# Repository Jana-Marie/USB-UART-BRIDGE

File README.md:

# USB-UART-BRIDGE

Smol and friendly USB-UART-BRIDGE & ESP32 programmer with Tag-Connect 2030 Connector :3

[KiCAD lib](https://github.com/Jana-Marie/ESP-TC-PROG/tree/main/KiCAD-libs)

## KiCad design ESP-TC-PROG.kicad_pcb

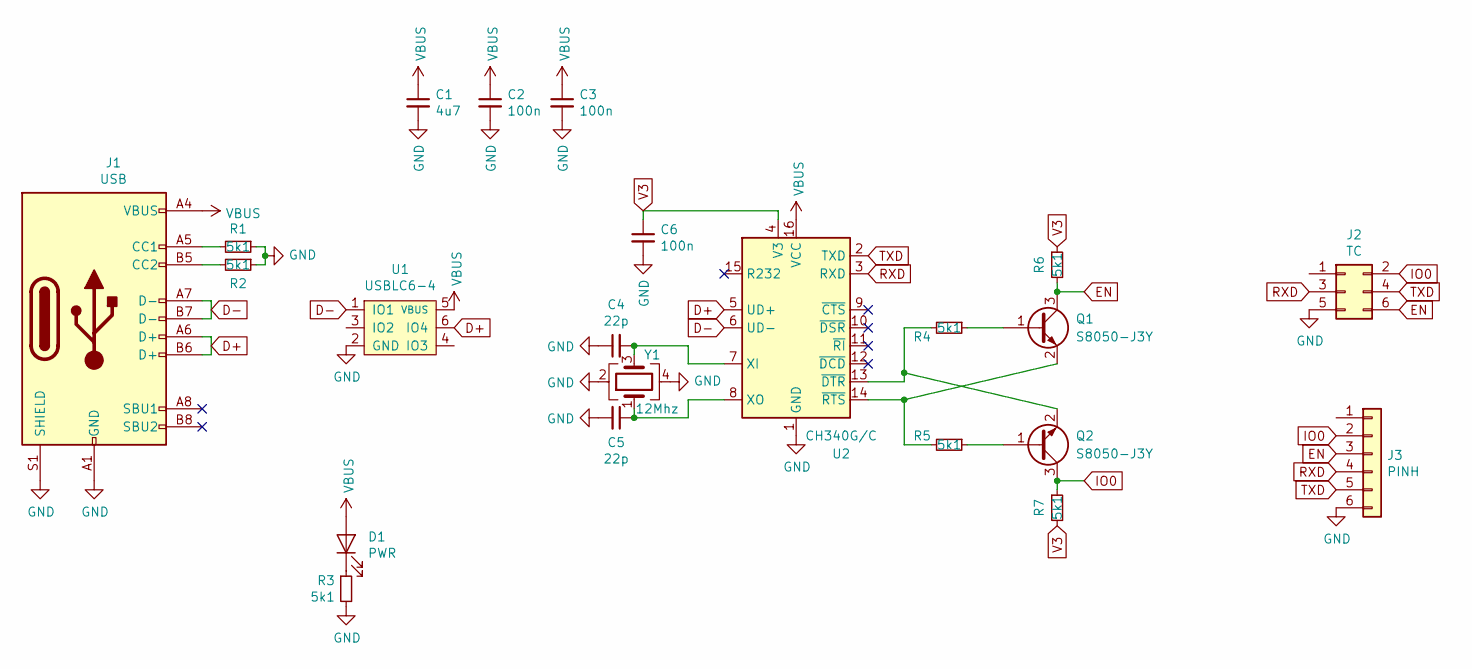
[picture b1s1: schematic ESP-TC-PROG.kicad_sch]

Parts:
C1: 4u7; C_0805
C2, C3, C6: 100n; C_0402
C4, C5: 22p; C_0402
D1: PWR; LED_0603_1608Metric
J1: USB; USB-C 16Pin
J2: TC; IDC-Header_2x03_P2.54mm_Vertical_center
J3: PINH; PinHeader_1x06_P2.54mm_Vertical_center
Q1, Q2: S8050-J3Y; SOT-23
R1, R2, R3, R4, R5, R6, R7: 5k1; R_0402
U1: USBLC6-4; SOT-23-6
U2: CH340G/C; SOIC-16_3.9x9.9mm_P1.27mm
Y1: 12Mhz; Crystal_SMD_3225-4Pin_3.2x2.5mm

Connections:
D+: J1.A6 (D+), J1.B6 (D+), U1.6 (IO4), U2.5 (UD+)
D-: J1.A7 (D-), J1.B7 (D-), U1.1 (IO1), U2.6 (UD-)
EN: J2.6, J3.3, Q1.3 (C), R6.2
GND: C1.2, C2.2, C3.2, C4.1, C5.2, C6.2, J1.A1 (GND), J1.A12 (GND), J1.B1 (GND), J1.B12 (GND), J1.S1 (SHIELD), J2.5, J3.6, R1.1, R2.1, R3.2, U1.2 (GND), U2.1 (GND), Y1.2, Y1.4
IO0: J2.2, J3.2, Q2.3 (C), R7.1
unnamed: C4.2, U2.7 (XI), Y1.3
unnamed: C5.1, U2.8 (XO), Y1.1
unnamed: D1.1 (K), R3.1
unnamed: J1.A5 (CC1), R1.2
unnamed: J1.B5 (CC2), R2.2
unnamed: Q1.1 (B), R4.1
unnamed: Q1.2 (E), R5.2, U2.14 (~RTS)
unnamed: Q2.1 (B), R5.1
unnamed: Q2.2 (E), R4.2, U2.13 (~DTR)
RXD: J2.3, J3.4, U2.3 (RXD)
TXD: J2.4, J3.5, U2.2 (TXD)
V3: C6.1, R6.1, R7.2, U2.4 (V3)
VBUS: C1.1, C2.1, C3.1, D1.2 (A), J1.A4 (VBUS), J1.A9 (VBUS), J1.B4 (VBUS), J1.B9 (VBUS), U1.5 (VBUS), U2.16 (VCC)

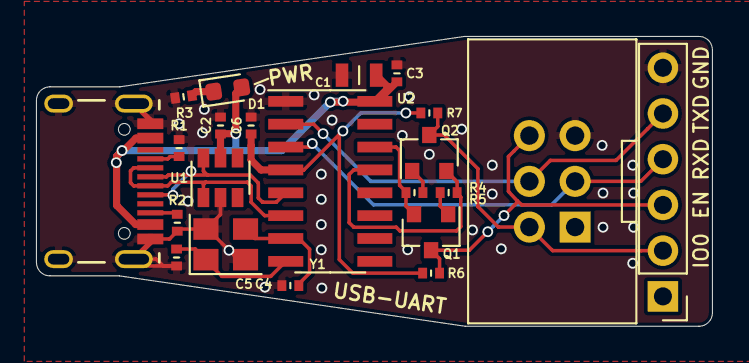
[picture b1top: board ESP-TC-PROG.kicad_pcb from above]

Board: 2 copper layers, 37.6 x 16.1 mm, 22 parts (0 on the bottom side), 18 nets.

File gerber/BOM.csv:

Comment,Designator,Footprint,LCSC
10µ,C1,otter:C_0603,C19702
0.1µ,"C3,C2,C6",otter:C_0402,C1525
22p,"C5,C4",otter:C_0402,C1555
PWR,D1,LED_SMD:LED_0603_1608Metric,C72043
USB,J1,otter:USB-C 16Pin,
TC,J2,otter:IDC-Header_2x03_P2.54mm_Vertical_center,
PINH,J3,otter:PinHeader_1x06_P2.54mm_Vertical_center,
AO3400A,"Q1,Q2",Package_TO_SOT_SMD:SOT-23,C20917
AO3401A,Q3,Package_TO_SOT_SMD:SOT-23,C15127
5k1,"R1,R2,R4,R5,R3",otter:R_0402,C25905
100k,R6,otter:R_0402,C25741
USBLC6-4,U1,Package_TO_SOT_SMD:SOT-23-6,C84837
CH340G,U2,otter:SOIC-16_3.9x9.9mm_P1.27mm,C14267
12Mhz,Y1,Crystal:Crystal_SMD_3225-4Pin_3.2x2.5mm,C9002

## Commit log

2020-03-14 added gitignore
2020-03-14 finalized silk
2020-03-14 export greber
2020-03-14 added edgerails + merged gerber
2020-03-15 added images
2020-04-02 removed old files
2020-04-04 updated files
2022-01-09 updated files to kicad 6
2022-04-26 added KiCAD lib and images
2023-01-01 updated gitignore
2023-01-01 renamed project
2023-01-01 removed gerber
2023-01-01 updated to v1.2.1
